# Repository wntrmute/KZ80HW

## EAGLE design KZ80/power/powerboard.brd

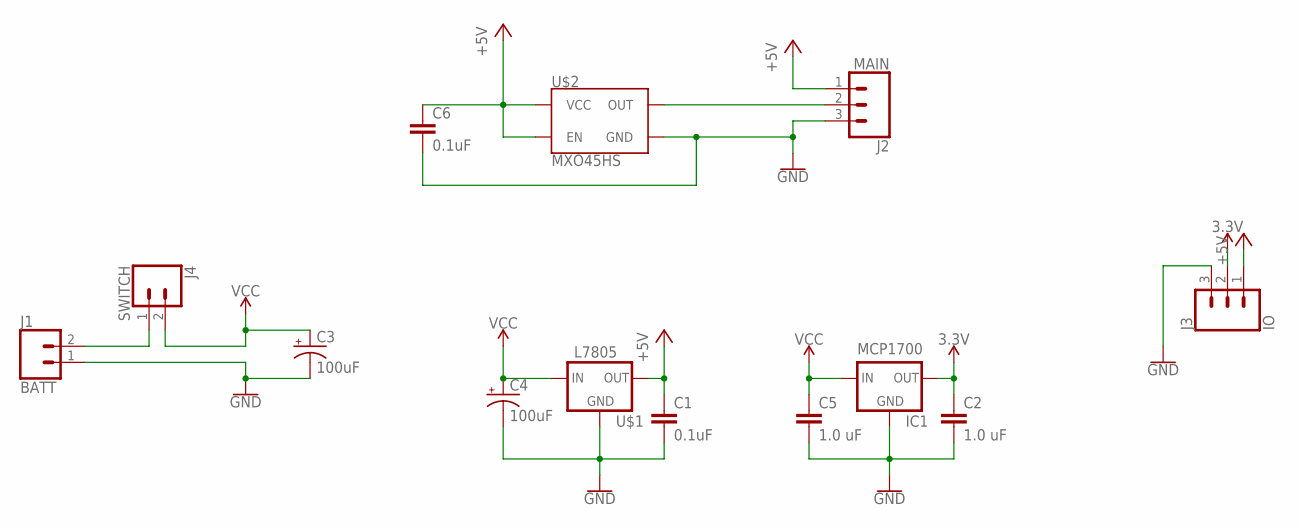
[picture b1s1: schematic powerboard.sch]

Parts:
C1, C6: 0.1uF; C2.5-3
C2, C5: 1.0 uF; C2.5-3
C3, C4: 100uF; CPOL-RADIAL-2.5MM-6.5MM
IC1: MCP1700; TO-92-AMMO
J1: BATT; SCREWTERMINAL-5MM-2
J2: MAIN; SCREWTERMINAL-5MM-3
J3: IO; SCREWTERMINAL-5MM-3
J4: SWITCH; 1X02
U$1: L7805; TO-220-FLAT
U$2: MXO45HS; DIL08-HALF

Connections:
3.3V: C2.1, IC1.3 (OUT), J3.2
+5V: C1.1, C6.1, J2.1, J3.1, U$1.OUT, U$2.1 (EN), U$2.8 (VCC)
GND: C1.2, C2.2, C3.2 (-), C4.2 (-), C5.2, C6.2, IC1.1 (GND), J1.1, J2.3, J3.3, U$1.GND, U$2.4 (GND)
unnamed: J1.2, J4.1
unnamed: J2.2, U$2.5 (OUT)
VCC: C3.1 (+), C4.1 (+), C5.1, IC1.2 (IN), J4.2, U$1.IN

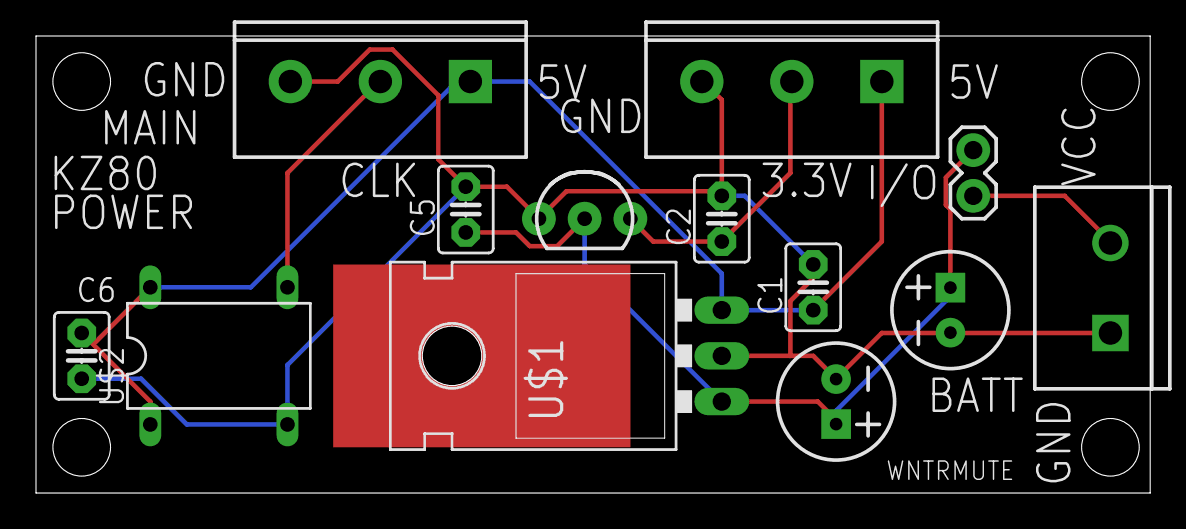
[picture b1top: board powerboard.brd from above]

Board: 2 copper layers, 61.9 x 25.4 mm, 13 parts (0 on the bottom side), 6 nets.

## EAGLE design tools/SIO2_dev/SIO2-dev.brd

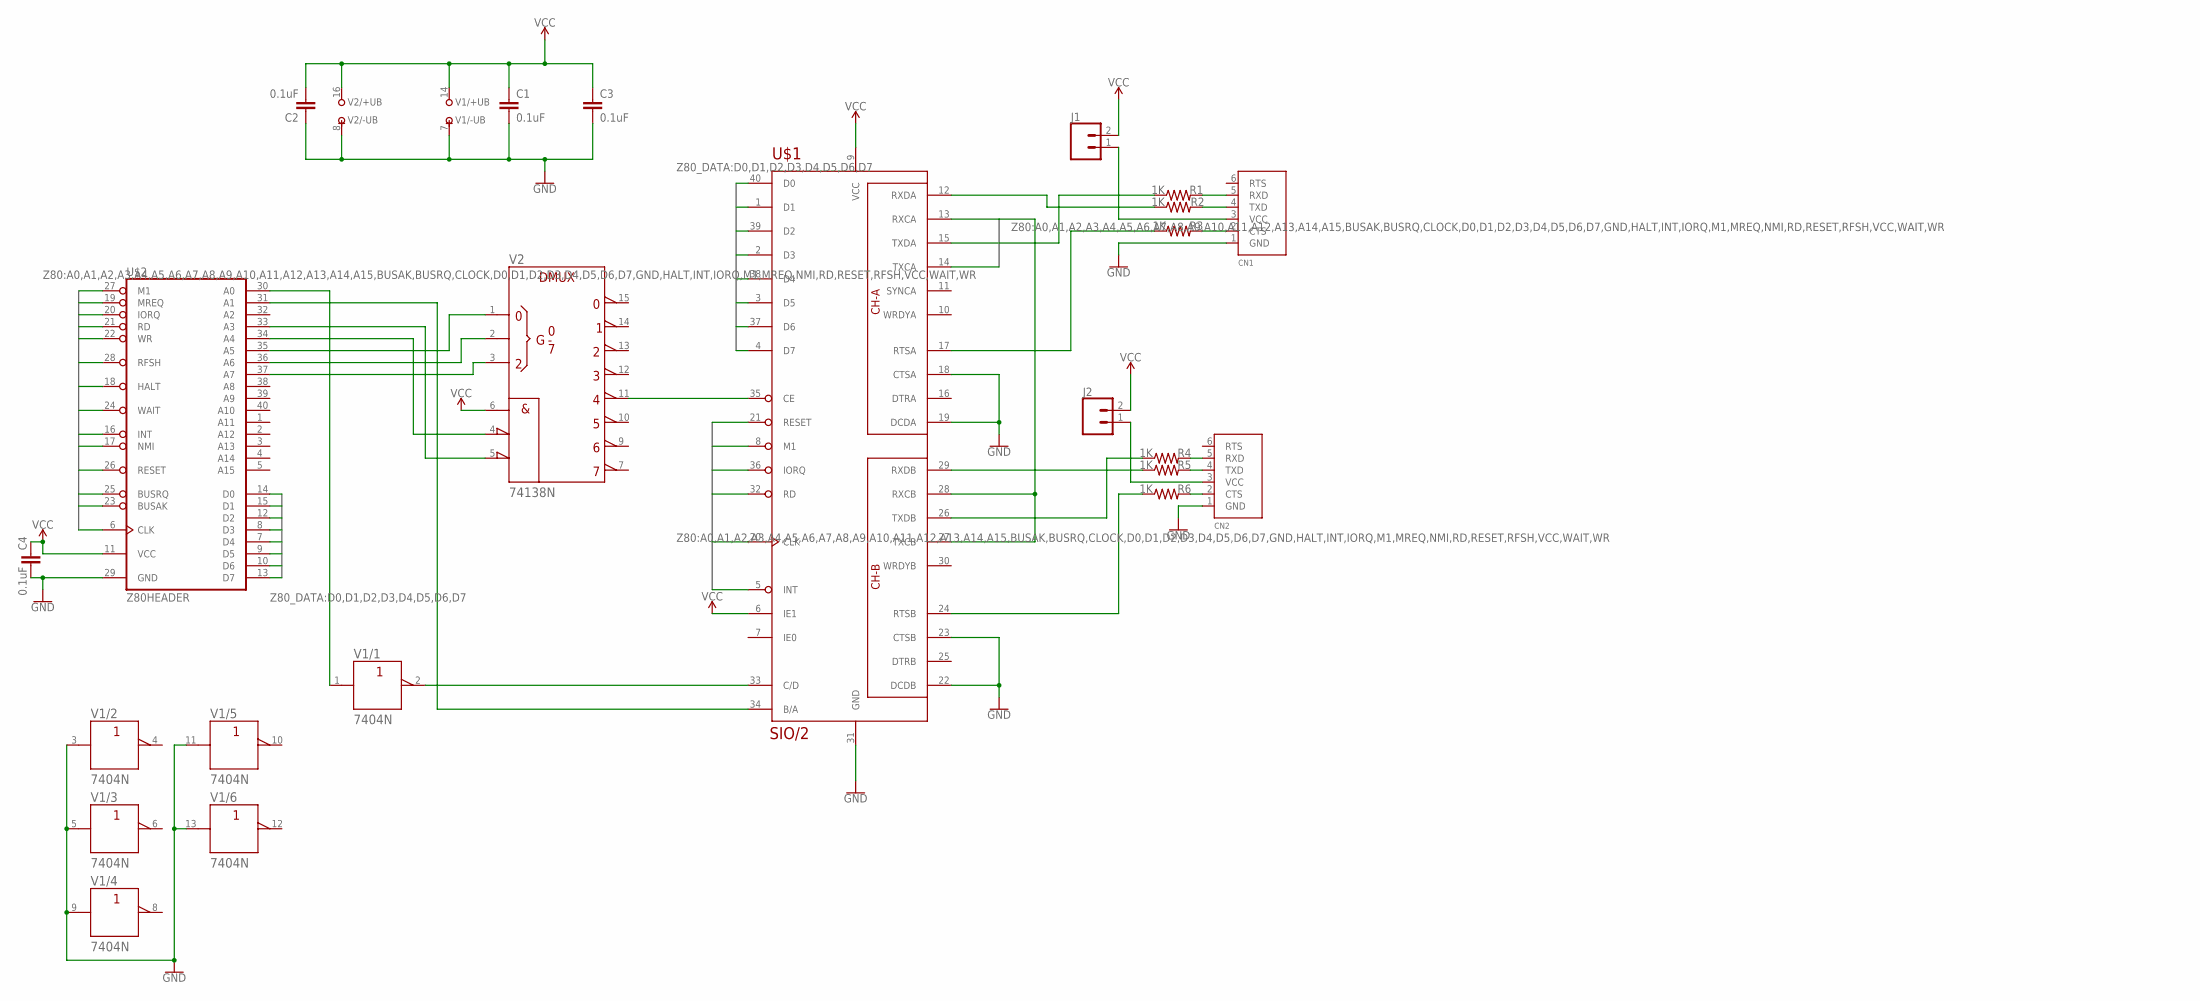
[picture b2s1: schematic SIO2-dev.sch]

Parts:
C1, C2, C3, C4: 0.1uF; C2.5-3
CN1, CN2: FTDIUSBCABLE; 1X06_ROUND
J1, J2: CONN_02; 1X02
R1, R2, R3, R4, R5, R6: 1K; AXIAL-0.3
U$1: SIO/2; DIL40
U$2: Z80HEADER; 2X20
V1: 7404N; DIL14
V2: 74138N; DIL16

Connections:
BUSAK: U$2.23 (BUSAK)
BUSRQ: U$2.25 (BUSRQ)
CLOCK: U$1.13 (RXCA), U$1.14 (TXCA), U$1.20 (CLK), U$1.27 (TXCB), U$1.28 (RXCB), U$2.6 (CLK)
D0: U$1.40 (D0), U$2.14 (D0)
D1: U$1.1 (D1), U$2.15 (D1)
D2: U$1.39 (D2), U$2.12 (D2)
D3: U$1.2 (D3), U$2.8 (D3)
D4: U$1.38 (D4), U$2.7 (D4)
D5: U$1.3 (D5), U$2.9 (D5)
D6: U$1.37 (D6), U$2.10 (D6)
D7: U$1.4 (D7), U$2.13 (D7)
GND: C1.2, C2.1, C3.2, C4.2, CN1.1 (GND), CN2.1 (GND), U$1.18 (CTSA), U$1.19 (DCDA), U$1.22 (DCDB), U$1.23 (CTSB), U$1.31 (GND), U$2.29 (GND), V1.3 (A), V1.5 (A), V1.7 (-UB), V1.9 (A), V1.11 (A), V1.13 (A), V2.8 (-UB)
HALT: U$2.18 (HALT)
INT: U$1.5 (INT), U$2.16 (INT)
IORQ: U$1.36 (IORQ), U$2.20 (IORQ)
M1: U$1.8 (M1), U$2.27 (M1)
MREQ: U$2.19 (MREQ)
unnamed: U$1.34 (B/A), U$2.31 (A1)
unnamed: U$1.35 (CE), V2.11 (Y4)
unnamed: U$2.30 (A0), V1.1 (A)
unnamed: U$1.33 (C/D), V1.2 (Y)
unnamed: U$2.33 (A3), V2.5 (!G2B)
unnamed: U$2.34 (A4), V2.4 (!G2A)
unnamed: U$2.35 (A5), V2.1 (A)
unnamed: U$2.36 (A6), V2.2 (B)
unnamed: U$2.37 (A7), V2.3 (C)
unnamed: R2.P$1 (1), U$1.12 (RXDA)
unnamed: R1.P$1 (1), U$1.15 (TXDA)
unnamed: R3.P$1 (1), U$1.17 (RTSA)
unnamed: CN1.2 (CTS), R3.P$2 (2)
unnamed: CN1.4 (TXD), R2.P$2 (2)
unnamed: CN1.5 (RXD), R1.P$2 (2)
unnamed: R6.P$1 (1), U$1.24 (RTSB)
unnamed: R5.P$1 (1), U$1.29 (RXDB)
unnamed: CN2.4 (TXD), R5.P$2 (2)
unnamed: CN2.2 (CTS), R6.P$2 (2)
unnamed: CN2.5 (RXD), R4.P$2 (2)
unnamed: CN1.3 (VCC), J1.1
unnamed: CN2.3 (VCC), J2.1
unnamed: R4.P$1 (1), U$1.26 (TXDB)
NMI: U$2.17 (NMI)
RD: U$1.32 (RD), U$2.21 (RD)
RESET: U$1.21 (RESET), U$2.26 (RESET)
RFSH: U$2.28 (RFSH)
VCC: C1.1, C2.2, C3.1, C4.1, J1.2, J2.2, U$1.6 (IE1), U$1.9 (VCC), U$2.11 (VCC), V1.14 (+UB), V2.6 (G1), V2.16 (+UB)
WAIT: U$2.24 (WAIT)
WR: U$2.22 (WR)

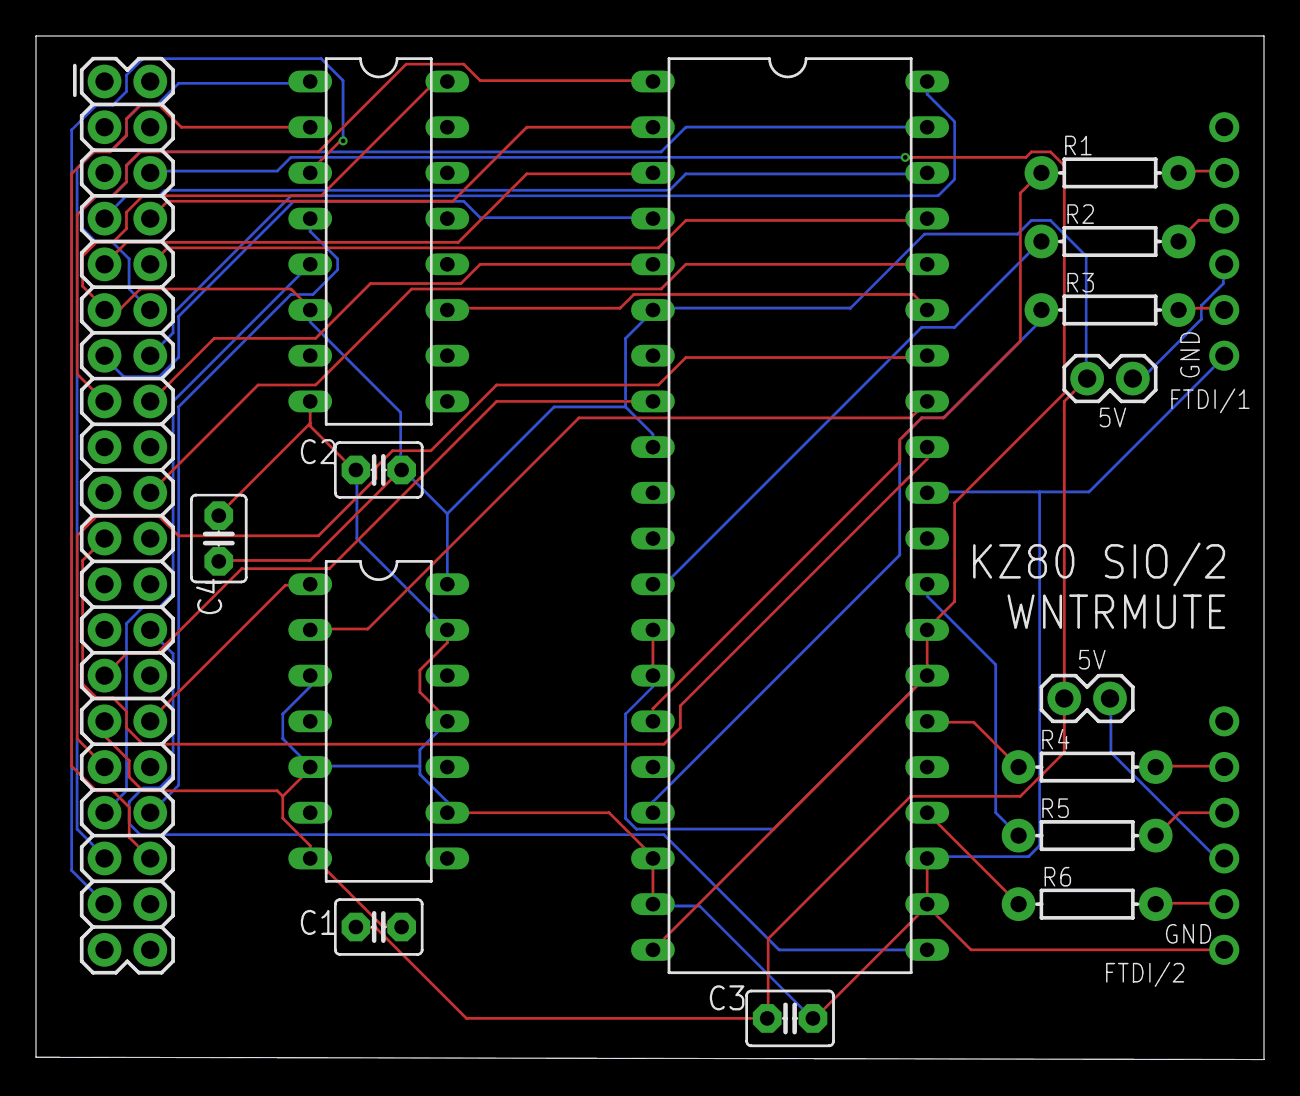
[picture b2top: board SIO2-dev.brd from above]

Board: 2 copper layers, 68.2 x 56.9 mm, 18 parts (0 on the bottom side), 39 nets.

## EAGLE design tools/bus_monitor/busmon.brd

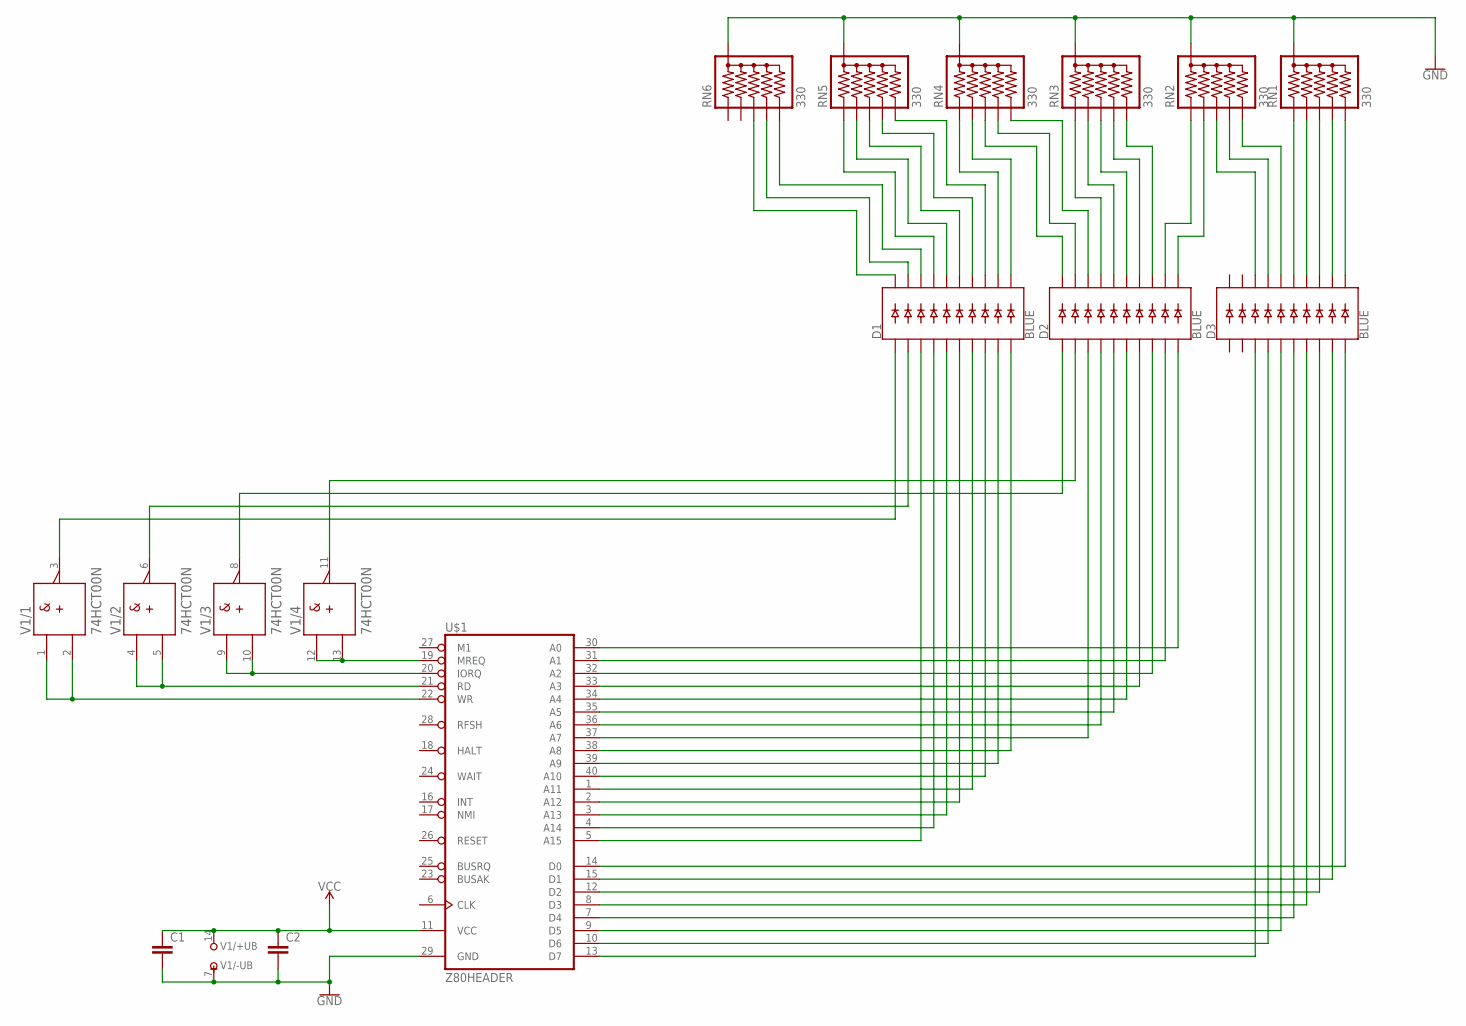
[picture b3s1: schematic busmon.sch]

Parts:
C1, C2: C2,5-3; C2.5-3
D1, D2, D3: BLUE; LED_BARGRAPH_10
RN1, RN2, RN3, RN4, RN5, RN6: 330; RPACK-SIP-PTH-5
U$1: Z80HEADER; 2X20
V1: 74HCT00N; DIL14

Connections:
GND: C1.2, C2.2, RN1.P$1 (1), RN2.P$1 (1), RN3.P$1 (1), RN4.P$1 (1), RN5.P$1 (1), RN6.P$1 (1), U$1.29 (GND), V1.7 (-UB)
unnamed: D2.2 (A1), V1.11 (Y)
unnamed: D2.1 (A), V1.8 (Y)
unnamed: D1.2 (A1), V1.6 (Y)
unnamed: D2.10 (A9), U$1.30 (A0)
unnamed: D1.1 (A), V1.3 (Y)
unnamed: D2.9 (A8), U$1.31 (A1)
unnamed: D2.8 (A7), U$1.32 (A2)
unnamed: D2.7 (A6), U$1.33 (A3)
unnamed: D2.6 (A5), U$1.34 (A4)
unnamed: D2.5 (A4), U$1.35 (A5)
unnamed: D2.4 (A3), U$1.36 (A6)
unnamed: D2.3 (A2), U$1.37 (A7)
unnamed: D1.10 (A9), U$1.38 (A8)
unnamed: D1.9 (A8), U$1.39 (A9)
unnamed: D1.8 (A7), U$1.40 (A10)
unnamed: D3.10 (A9), U$1.14 (D0)
unnamed: D3.9 (A8), U$1.15 (D1)
unnamed: D3.8 (A7), U$1.12 (D2)
unnamed: D3.7 (A6), U$1.8 (D3)
unnamed: D3.6 (A5), U$1.7 (D4)
unnamed: D3.5 (A4), U$1.9 (D5)
unnamed: D3.4 (A3), U$1.10 (D6)
unnamed: D3.3 (A2), U$1.13 (D7)
unnamed: U$1.19 (MREQ), V1.12 (A), V1.13 (B)
unnamed: D2.19 (C1), RN4.P$5 (5)
unnamed: U$1.20 (IORQ), V1.9 (A), V1.10 (B)
unnamed: U$1.21 (RD), V1.4 (A), V1.5 (B)
unnamed: U$1.22 (WR), V1.1 (A), V1.2 (B)
unnamed: D3.11 (C9), RN1.P$6 (6)
unnamed: D3.12 (C8), RN1.P$5 (5)
unnamed: D3.13 (C7), RN1.P$4 (4)
unnamed: D3.14 (C6), RN1.P$3 (3)
unnamed: D3.15 (C5), RN1.P$2 (2)
unnamed: D3.16 (C4), RN2.P$6 (6)
unnamed: D3.17 (C3), RN2.P$5 (5)
unnamed: D3.18 (C2), RN2.P$4 (4)
unnamed: D2.11 (C9), RN2.P$3 (3)
unnamed: D2.12 (C8), RN2.P$2 (2)
unnamed: D2.13 (C7), RN3.P$6 (6)
unnamed: D2.14 (C6), RN3.P$5 (5)
unnamed: D2.15 (C5), RN3.P$4 (4)
unnamed: D2.16 (C4), RN3.P$3 (3)
unnamed: D2.17 (C3), RN3.P$2 (2)
unnamed: D2.18 (C2), RN4.P$6 (6)
unnamed: D2.20 (C), RN4.P$4 (4)
unnamed: D1.11 (C9), RN4.P$3 (3)
unnamed: D1.17 (C3), RN5.P$2 (2)
unnamed: D1.12 (C8), RN4.P$2 (2)
unnamed: D1.13 (C7), RN5.P$6 (6)
unnamed: D1.18 (C2), RN6.P$6 (6)
unnamed: D1.14 (C6), RN5.P$5 (5)
unnamed: D1.7 (A6), U$1.1 (A11)
unnamed: D1.15 (C5), RN5.P$4 (4)
unnamed: D1.16 (C4), RN5.P$3 (3)
unnamed: D1.6 (A5), U$1.2 (A12)
unnamed: D1.19 (C1), RN6.P$5 (5)
unnamed: D1.20 (C), RN6.P$4 (4)
unnamed: D1.5 (A4), U$1.3 (A13)
unnamed: D1.4 (A3), U$1.4 (A14)
unnamed: D1.3 (A2), U$1.5 (A15)
VCC: C1.1, C2.1, U$1.11 (VCC), V1.14 (+UB)

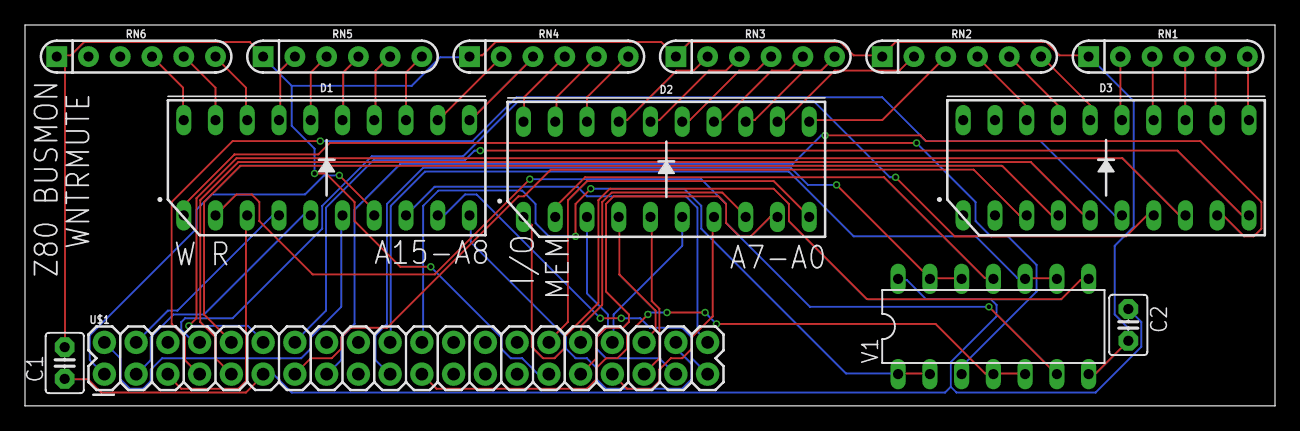
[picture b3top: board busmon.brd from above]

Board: 2 copper layers, 100.0 x 30.5 mm, 13 parts (0 on the bottom side), 62 nets.

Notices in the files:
parts and their libraries:
SparkFun-Capacitors: Licensing: Creative Commons ShareAlike 4.0 International - https://creativecommons.org/licenses/by-sa/4.0
microbuilder: This work is placed in the public domain, and may be freely used for commercial and non-commercial work with the following conditions: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
